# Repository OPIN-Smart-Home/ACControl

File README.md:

# OPIN AC Control

## Table of Contents
For User
- [Introduction](#introduction)
- [Features](#features)
- [Components and Interface](#components-and-interface)
- [User Guide](#user-guide)

For Developer
- [Installation](#installation)
- [MQTT Topics](#mqtt-topics)
- [Limitations](#limitations)
- [Future Development](#future-development)

Additional Information
- [OPIN Smart Home Devices](#opin-smart-home-devices)
- [Acknowledgments](#acknowledgments)
- [Further Information](#further-information)

 ---
 ---

# For User
## Introduction
The OPIN AC Control is an innovative solution designed to enhance the comfort and convenience of managing air conditioning systems in homes and offices. Integrated with the [OPIN Gateway](https://github.com/OPIN-Smart-Home/OPIN-JetsonNano-public), this device allows users to control their AC units remotely through the OPIN mobile app.

With the OPIN AC Control, users can easily turn their air conditioning units on or off, adjust temperature settings, manage swing and fan settings, and benefit from the auto-off feature for energy savings—all from anywhere, providing flexibility and control over their indoor environment. The device is compatible with various AC models, as it forwards received IR data to and from the gateway, ensuring up-to-date control across all devices.

The OPIN AC Control features real-time monitoring of room temperature and humidity, enabling users to maintain a comfortable atmosphere in their spaces. Additionally, notifications regarding system status ensure that users are always informed of their AC's performance and settings.

For developers, the OPIN AC Control utilizes the MQTT protocol for seamless communication, enabling easy integration with other smart devices within the OPIN ecosystem. With its user-friendly interface, reliable performance, energy-saving features, and advanced functionalities, the OPIN AC Control is the perfect solution for modern living.

## Features
The OPIN AC Control offers a range of features to make managing air conditioners more convenient and efficient:
1. **Remote Control via Mobile App**:  
   Control your air conditioner from anywhere using the OPIN mobile app. Adjust temperature, change fan speed, and control swing settings with ease.
2. **Real-Time Room Monitoring**:  
   Equipped with a BME280 sensor, the device provides real-time monitoring of room temperature and humidity, giving you insights to optimize your indoor comfort.
3. **Eco-Friendly Power Source**:  
   Powered by a rechargeable 18650 battery, the device is both eco-friendly and cost-effective. With up to 18 hours of battery life on a single charge, the device ensures continuous operation without the need for disposable batteries.
4. **Auto-Off Feature**:  
   The OPIN AC Control supports an auto-off function, automatically turning off the air conditioner after a specified period of inactivity, reducing energy consumption and saving costs.
5. **Sync with Original Remote**:  
   Capable of reading IR data from the original remote control, the OPIN AC Control can update settings in the mobile app, ensuring that all configurations are synced with the user's preferences.
6. **Battery and Charging Monitoring**:  
   The device features LED indicators for charging and full-charge status, ensuring you always know when it’s time to recharge.
7. **Seamless Integration**:  
    Utilizes the MQTT protocol for smooth communication with the OPIN ecosystem, allowing for easy integration with other smart devices.

## Components and Interface
The following components are used in the OPIN AC Control. The numbers correspond to the labels in the [cover image](#opin-ac-control):
1. [**ESP32 Devkit V1**](<https://olddocs.zerynth.com/r2.3.3/official/board.zerynth.doit_esp32/docs/index.html>)  
   The microcontroller responsible for managing the device's operations and communication via MQTT. It processes signals from the IR transmitter and receiver to control the AC unit.
2. **IR Transmitter**  
   This component sends infrared signals to the AC unit, allowing remote control of its functions, such as temperature settings, fan speed, and swing direction.
3. **IR Receiver**  
   The IR receiver captures signals from the original remote control, allowing the OPIN AC Control to send temperature settings, fan speed, and swing direction data to the app, ensuring that the information is synchronized and up to date.
4. **LED**  
   The device features an LED that indicates the Wi-Fi connection status, helping users verify whether the device is connected to the network.
5. **Button**  
   A button is provided for initiating the Wi-Fi configuration process, allowing users to connect the device to their network. This button can also be used to reset the Wi-Fi connection.
6. **J5019 Charging Module**  
   The J5019 charging module features a Micro USB input terminal, allowing direct connection to a phone charger for recharging lithium batteries. It supports charging and discharging protection for various lithium batteries, including 18650 and polymer batteries with a nominal voltage of 3.6V to 3.7V.
7. **BME280 Sensor**  
   This sensor measures temperature and humidity levels in the room, providing real-time data to users through the mobile app.
8. **18650 Battery Flat Top Holder**  
   A holder for the rechargeable 18650 battery flat top, ensuring safe and secure placement within the device.
9. **Charging Port**  
   This port allows users to recharge the built-in 18650 battery, ensuring continuous operation.
10. **On/Off Switch**  
    A switch that enables users to manually power the device on or off as needed.
11. **MAX17048**  
    A battery fuel gauge that monitors the battery level and provides information about the remaining power, enhancing the user experience.
12. **Device Holder**  
   The device holder is designed to resemble the original remote control, providing a familiar and ergonomic grip. It securely houses all components of the OPIN AC Control, ensuring stability and a clean aesthetic while facilitating easy handling and operation.

## User Guide
This section provides step-by-step instructions on how to set up and use the OPIN kWh Meter effectively.
### 1. Initial Setup
   - **Insert the Battery**: Place a 18650 battery flat top into the battery holder. Ensure it is oriented correctly, following the polarity markings.
   - **Power On the Device**: Use the on/off switch to power on the OPIN AC Control.
   - **Position the OPIN AC Control**:  
     Mount or place the OPIN AC Control near the AC unit for optimal IR communication. The device should have a clear line of sight to the AC unit.

### 2. LED Indicator
1. **Solid**: The device is connected to the network.
2. **Blinking continuously**: The device is not connected to a network or in the process of connecting.
3. **Off**: The device is either not powered or in WiFi configuration mode.

### 3. WiFi Configuration
#### Add WiFi Configuration
1. **Initiate WiFi Configuration**  
   - Press the button once to enter WiFi configuration mode. The LED will blink twice, indicating that the device is ready to connect to a network.  

2. **Connect to the Network**  
   - Open the WiFi settings on your mobile, laptop, or PC.
   - Connect to the AC Control SSID `OPIN-ACControl-[device_id]`. Your device should automatically redirect you to the WiFi configuration interface (captive portal).
      > **Tips**: If you're not redirected to the captive portal automatically, try the following:  
      (1) Look for a notification asking you to `log in to the network`,  
      (2) Go to [WiFi settings](<https://media.techietech.tech/2020/06/Forget-Network.jpg.webp>) and select something like `Manage network settings`,  
      (3) Manually access the captive portal by opening `192.168.4.1` in your browser.
   - Once inside the configuration interface, select `Configure WiFi`. Choose your home WiFi SSID from the list, enter the password, and click `Save`. (Refer to the provided images for detailed guidance.)  

3. **Confirm Connection**  
   - After the connection is established, the LED will turn solid, indicating that the AC Control is successfully connected to your WiFi network.

#### Reset WiFi Configuration
1. **Initiate Reset**  
   - Press and hold the button for at least two seconds. The LED will blink three times (indicating reset) followed by two blinks (entering WiFi configuration mode), signaling that the WiFi settings have been reset. This action will erase all previously saved WiFi configurations.  

2. **Reconnect to the Network**  
   - After resetting the WiFi, follow step [2 "Connect to the Network"](#add-WiFi-configuration) from the **Add WiFi Configuration** section to reconnect the AC Control to your WiFi.

#### Check IP Address of the AC Control
1. **Initiate WiFi Configuration**  
   - Press the button once to enter WiFi configuration mode. The LED will blink twice, indicating that the device is ready for network configuration.  

2. **Connect to the Network**  
   - Open the WiFi settings on your mobile, laptop, or PC.
   - Connect to the AC Control SSID `OPIN-ACControl-[device_id]`, and your device will be redirected to the WiFi configuration interface (captive portal).  
      > **Tip**: If you're not redirected to the captive portal automatically, try the following:  
      (1) Look for a notification asking you to `log in to the network`,  
      (2) Go to [WiFi settings](<https://media.techietech.tech/2020/06/Forget-Network.jpg.webp>) and select `Manage network settings`,  
      (3) Manually access the captive portal by opening `192.168.4.1` in your browser.
   - The IP address of the AC Control will be shown in the connected WiFi details box. (Refer to the provided image for reference.)  

3. **Exit Configuration Mode**  
   - After checking the IP address, select `Exit` to complete the configuration process. The LED will turn solid, indicating that the AC Control is successfully connected to your WiFi network.

### 4. Connect AC Control to OPIN Mobile App
1. **Add New Device**  
   - Open the OPIN mobile app and click the `Add New Device` option.  
   - Select `AC Control` from the list of devices.  
   - Enter the `Device ID` and `IP Address` of the AC Control.   
   - Click `Submit`.  
   > **Note**: Ensure that the `Device ID` and `IP Address` are accurate to avoid issues during the device setup.

2. **Control the AC Unit**
   - **Use the Original IR Remote Control**: Point your original AC remote at the AC unit and OPIN AC Control to set and send the current temperature settings, fan speed, and swing direction. The device will sync this information with the mobile app.  
     
   - **Adjust Settings via Mobile App**: Use the OPIN mobile app to control your AC settings remotely, including turning the unit on or off and adjusting temperature preferences.  
   - **Auto Off Feature**: The OPIN AC Control also supports an `Auto Off` feature, which automatically turns off the AC unit when no person is detected in the room, helping save energy. You can enable and manage this feature through the OPIN mobile app. For more details, refer to the [Auto Off feature documentation](https://github.com/OPIN-Smart-Home/OPIN-JetsonNano-public#auto-off-feature).

4. **Monitoring Room Conditions**
   - **View Real-Time Data**: The OPIN AC Control provides real-time monitoring of room temperature and humidity via the app, allowing users to stay informed about their indoor environment.

5. **Charging Instructions**
   - **Connect the Charging Module**:    
     Use a Micro USB cable to connect the J5019 charging module to a power source (like a phone charger) to charge the 18650 lithium battery. While charging, the LED indicator will show **red**.  
       
   - **Charging Duration**: Charging typically takes 4 hours. Check the battery indicator to monitor the charging status.  
   - **Fully Charged Indicator**:  
     Once the battery is fully charged, the LED indicator will turn **green**.  
       
   - **Battery Life**: The 18650 battery usually lasts for about 18 hours of continuous operation. Ensure to recharge it regularly to maintain functionality.

### 5. Troubleshooting
1. **Device Not Connecting to Wi-Fi**
   - **Check Wi-Fi Credentials**: Ensure that the correct Wi-Fi credentials (SSID and password) are entered during the setup.
   - **Proximity to Router**: Make sure the kWh Meter is within the range of your Wi-Fi router. Try moving it closer to the router for better signal strength.
   - **Reboot the Device**: Restart the OPIN AC Control by toggling the on/off switch.

2. **App Not Displaying Data**
   - **Check Device ID and IP Address**: Ensure that the correct Device ID and IP address are entered in the app. Incorrect entries can prevent data from being displayed.

---
---

# For Developer
This section provides guidelines for developers looking to contribute to the OPIN Smart Home system. It's recommended to pay attention on [For User](#for-user) section.
## Installation
### Prerequisites
Before you begin, ensure you have the following installed on your development environment:
- **Arduino IDE** for uploading the firmware to the ESP32.
- **ESP32 Board Package** for Arduino IDE. For Arduino IDE, you can install it by going to **File > Preferences > Additional Board Manager URLs** and adding `https://dl.espressif.com/dl/package_esp32_index.json`. Then, navigate to **Tools > Board > Board Manager** and search for "ESP32".
- **Required Libraries**:
  - **WiFi**: For WiFi connectivity.
  - **Wire**: Provides communication over I2C between the microcontroller and sensors.
  - [**IRremoteESP8266** by David Conran, et al.](<https://github.com/crankyoldgit/IRremoteESP8266>) version `2.8.6`
    - **IRac**: For controlling and interacting with the air conditioning system via infrared signals.
    - **IRsend**: Sends IR signals to the AC unit for control.
    - **IRrecv**: Receives IR signals from the original AC remote.
  - [**PicoMQTT** by Michał Leśniewski](<https://github.com/mlesniew/PicoMQTT>) version `0.3.8` : To enable the ESP32 to function as an MQTT broker/server.
  - [**WiFiManager** by tzapu](<https://github.com/tzapu/WiFiManager>) version `2.0.17`: For handling WiFi connections and configurations.
  - [**Adafruit BME280** by Adafruit](<https://github.com/adafruit/Adafruit_BME280_Library>) version `2.2.2`: For monitoring room temperature and humidity.
  - [**Adafruit MAX1704X** by Adafruit](<https://github.com/adafruit/Adafruit_MAX1704X>) version `1.0.3`: For monitoring battery status.

### Clone the Repository
To get started with the project, clone the repository to your local machine:
```bash
git clone https://github.com/OPIN-Smart-Home/ACControl.git
```

## MQTT Topics
The OPIN AC Control communicates with the OPIN Gateway using the following MQTT topics:
- **Remote to User (r2u)**:  
  `opin/ACControl_[device_id]/r2u`  
  This topic is used to send IR data captured from the original AC remote control back to the user. It ensures that the AC settings, such as temperature, fan speed, and swing direction, are up-to-date in the OPIN mobile app.
- **Device to User (d2u)**:  
  `opin/ACControl_[device_id]/d2u`  
  The topic for sending device status, such as the current room temperature, humidity, and battery level, to the user via the OPIN mobile app.
- **User to Device (u2d)**:  
  `opin/ACControl_[device_id]/u2d`  
  This topic is used for sending control commands from the user to the OPIN AC Control, allowing users to adjust the AC settings like turning it on/off, setting the temperature, or adjusting the fan speed and swing direction.
- **Device SSID**:  
  `OPIN-ACControl-[device_id]`  
  This SSID is used when connecting the OPIN AC Control to Wi-Fi during the initial configuration process.
> **Note**: Each AC control device must have a unique `device_id`. This prevents conflicts when multiple devices are connected within the OPIN ecosystem.

## Limitations
While the OPIN AC Control offers a range of convenient features for controlling air conditioners, it does have certain limitations that users should be aware of:
1. **Limited Battery Life**:  
   The 18650 rechargeable battery provides up to 18 hours of operation on a full charge. Users may need to recharge the device daily if used extensively. Additionally, battery performance may degrade over time, reducing operational hours between charges.
2. **Dependent on Line of Sight**:  
   Since the OPIN AC Control uses IR signals to communicate with the air conditioner, it requires a clear line of sight between the device and the AC unit. Obstructions may cause the signal to fail, preventing remote control of the AC.
3. **Wi-Fi Configuration Required**:  
   The device must be connected to the same local Wi-Fi network as the OPIN Gateway. If the device is moved to a different network, Wi-Fi configuration needs to be reset and reconfigured through the app.
4. **Manual Battery Charging**:  
   The device does not feature automatic charging capabilities. Users must manually plug the device into a power source via the charging port when the battery is low.

## Future Development
The OPIN AC Control is designed to evolve with user needs and technological advancements. Several improvements and new features are planned for future releases to enhance functionality and user experience:
1. **Longer Battery Life**:  
   Efforts are being made to improve the efficiency of the device’s power consumption. Future iterations may include the use of more advanced battery technology or power-saving features to extend operational hours beyond the current 18-hour limit.
2. **Voice Assistant Integration**:  
   The OPIN AC Control is expected to integrate with popular voice assistants such as Google Assistant and Amazon Alexa. This would enable users to control their AC units using voice commands, adding another layer of convenience to the smart home experience.
3. **Room Temperature and Humidity-Based Automation**:  
   In the future, the device could be programmed to automatically adjust the AC settings based on room temperature and humidity, creating a more comfortable and energy-efficient environment.

---
---

# Additional Information
## OPIN Smart Home Devices
Other devices:
- [OPIN Smart Gateway](<https://github.com/OPIN-Smart-Home/OPIN-JetsonNano-public>)
- [OPIN Smart Lamp](<https://github.com/OPIN-Smart-Home/SmartLamp>)
- [OPIN Smart kWh Meter](<https://github.com/OPIN-Smart-Home/kWhMeter>)
- [OPIN Smart Door Lock](<https://github.com/OPIN-Smart-Home/DoorLock>)

## Acknowledgments
This project makes use of:  
- [PicoMQTT](<https://github.com/mlesniew/PicoMQTT>) by [mlesniew](<https://github.com/mlesniew>) (Michał Leśniewski), under [LGPL-3.0 license](<https://github.com/mlesniew/PicoMQTT/blob/master/LICENSE>).
- [WiFiManager](<https://github.com/tzapu/WiFiManager>) by [tzapu](<https://github.com/tzapu>), under [MIT license](<https://github.com/tzapu/WiFiManager/blob/master/LICENSE>).
- [IRremoteESP8266](<https://github.com/crankyoldgit/IRremoteESP8266>) by [crankyoldgit](<https://github.com/crankyoldgit>) (David Conran), under [LGPL-2.1 license](<https://github.com/crankyoldgit/IRremoteESP8266/blob/master/LICENSE.txt>).
- [Adafruit_BME280_Library](<https://github.com/adafruit/Adafruit_BME280_Library>) by [adafruit](<https://github.com/adafruit>), under [license](<https://github.com/adafruit/Adafruit_BME280_Library/blob/master/LICENSE>).
- [Adafruit_MAX1704X](<https://github.com/adafruit/Adafruit_MAX1704X>) by [adafruit](<https://github.com/adafruit>), under [license](<https://github.com/adafruit/Adafruit_MAX1704X/blob/main/license.txt>).

We appreciate their efforts and contributions, which have been instrumental in the development of this project.

## Further Information
For further information, please feel free to contact me at:
- **Email**: [anisahfarah28@gmail.com](mailto:anisahfarah28@gmail.com)
- **LinkedIn**: [Anisah Farah Fadhilah](https://www.linkedin.com/in/anisahfarahfadhilah)

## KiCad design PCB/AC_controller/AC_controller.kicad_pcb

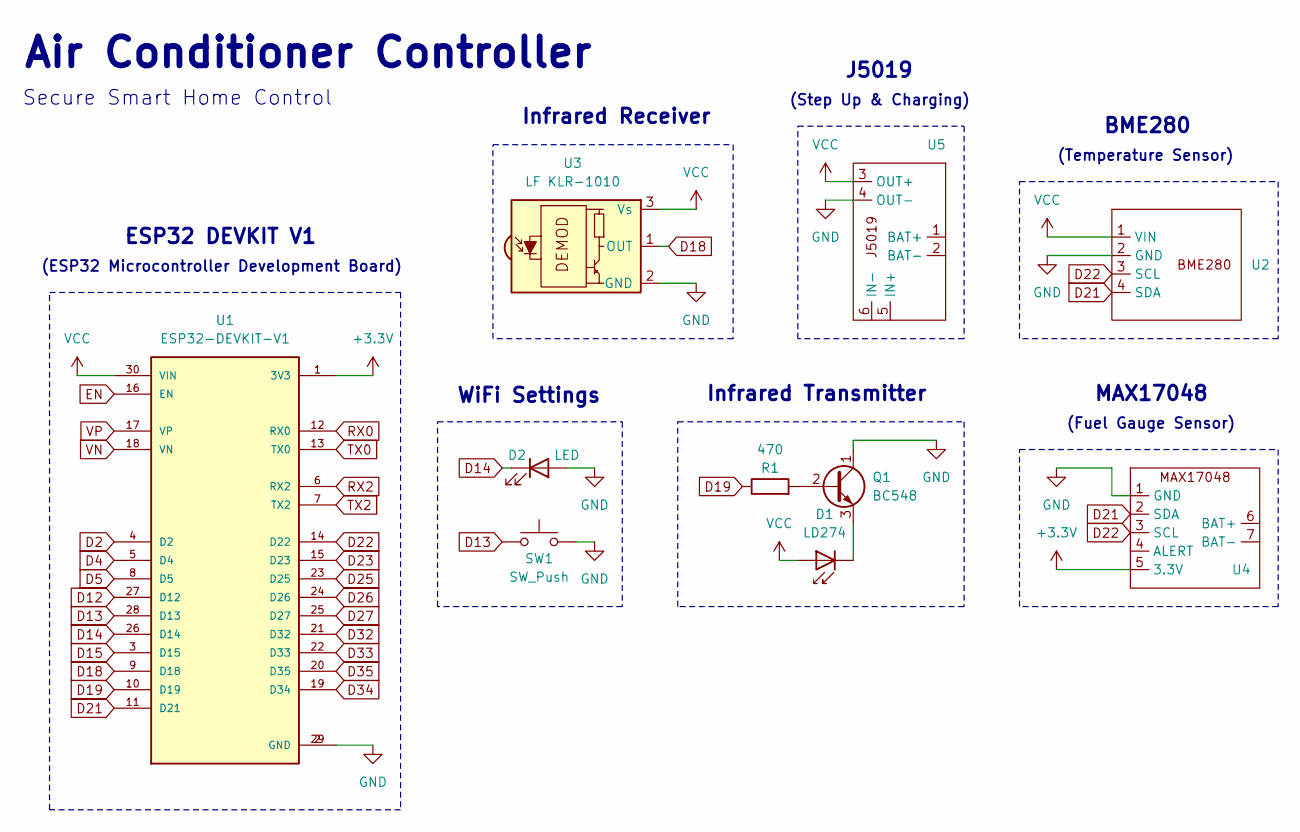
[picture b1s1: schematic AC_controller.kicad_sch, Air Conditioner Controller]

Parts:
D1: LD274; LED_D5.0mm_IRGrey
D2: LED; LED_D5.0mm_Clear
Q1: BC548; TO-92_Inline
R1: 470; R_Axial_DIN0207_L6.3mm_D2.5mm_P7.62mm_Horizontal
SW1: SW_Push; SW_PUSH_6mm_H9.5mm
U1: ESP32-DEVKIT-V1; MODULE_ESP32_DEVKIT_V1; PARTREV N/A
U2: module_bme280_alt
U3: LF KLR-1010; Vishay_MINICAST-3Pin
U4: max17048_pads
U5: j5019_pads

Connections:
+3.3V: U1.1 (3V3), U4.5 (3.3V)
D2: U1.4 (D2)
D4: U1.5 (D4)
D5: U1.8 (D5)
D12: U1.27 (D12)
D13: SW1.1, U1.28 (D13)
D14: D2.1 (K), U1.26 (D14)
D15: U1.3 (D15)
D18: U1.9 (D18), U3.1 (OUT)
D19: R1.1, U1.10 (D19)
D21: U1.11 (D21), U2.4 (SDA), U4.2 (SDA)
D22: U1.14 (D22), U2.3 (SCL), U4.3 (SCL)
D23: U1.15 (D23)
D25: U1.23 (D25)
D26: U1.24 (D26)
D27: U1.25 (D27)
D32: U1.21 (D32)
D33: U1.22 (D33)
D34: U1.19 (D34)
D35: U1.20 (D35)
EN: U1.16 (EN)
GND: D2.2 (A), Q1.1 (C), SW1.2, U1.2 (GND), U1.29 (GND), U2.2 (GND), U3.2 (GND), U4.1 (GND), U5.4 (OUT-)
unnamed: D1.1 (K), Q1.3 (E)
unnamed: Q1.2 (B), R1.2
RX0: U1.12 (RX0)
RX2: U1.6 (RX2)
TX0: U1.13 (TX0)
TX2: U1.7 (TX2)
VCC: D1.2 (A), U1.30 (VIN), U2.1 (VIN), U3.3 (Vs), U5.3 (OUT+)
VN: U1.18 (VN)
VP: U1.17 (VP)

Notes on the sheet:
(Fuel Gauge Sensor)
Secure Smart Home Control
ESP32 DEVKIT V1
BME280
WiFi Settings
Infrared Transmitter
(Step Up & Charging)
J5019
Infrared Receiver
(ESP32 Microcontroller Development Board)
(Temperature Sensor)
MAX17048
Air Conditioner Controller

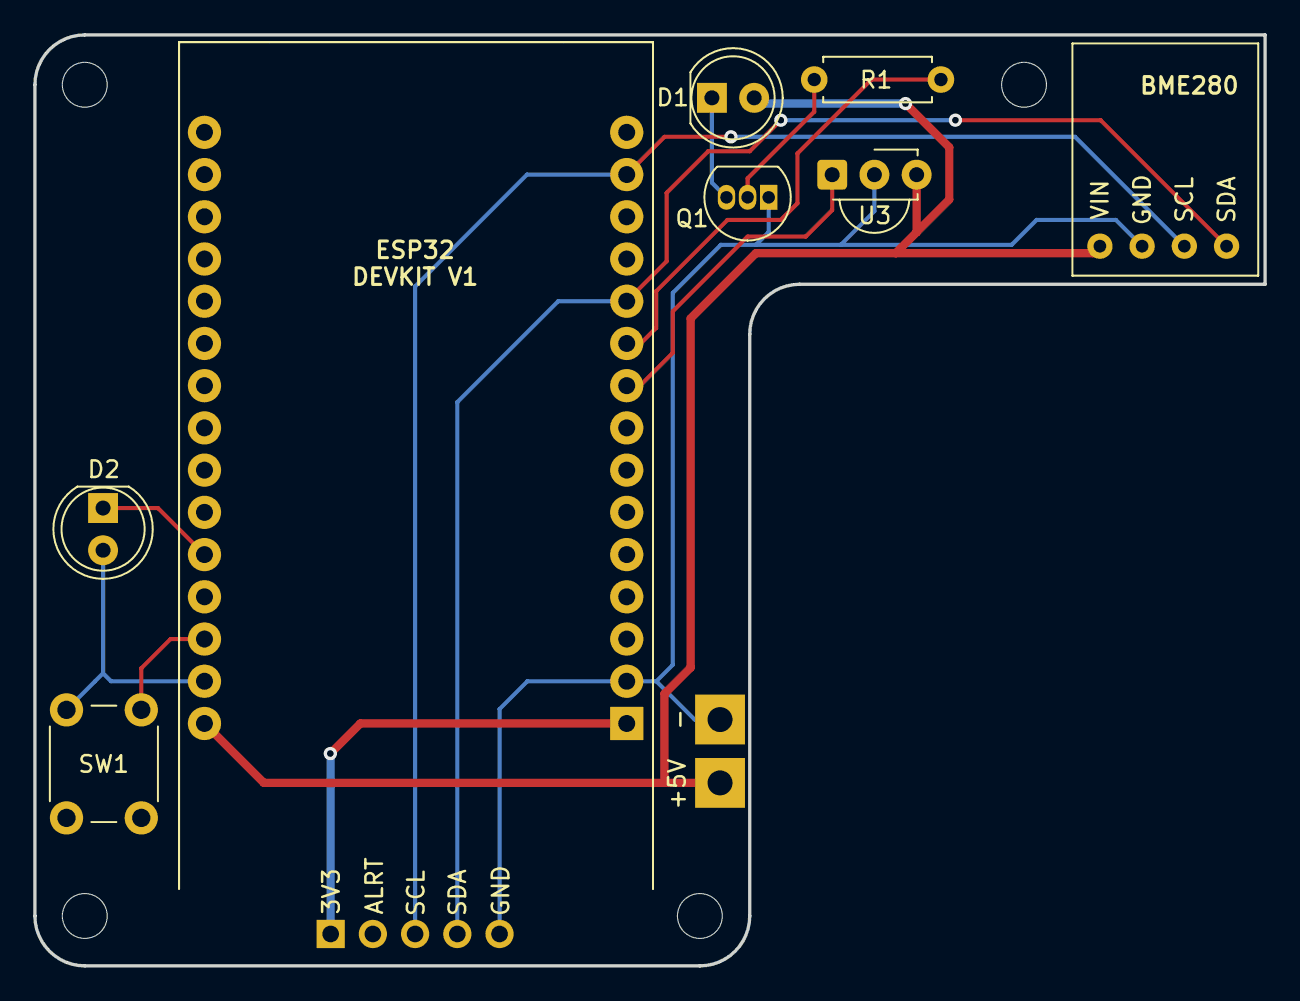
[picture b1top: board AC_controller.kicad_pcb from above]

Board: 2 copper layers, 74.0 x 56.0 mm, 10 parts (0 on the bottom side), 11 nets.

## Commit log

2024-10-07 Create LICENSE

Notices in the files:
README.md:
License: Apache 2
